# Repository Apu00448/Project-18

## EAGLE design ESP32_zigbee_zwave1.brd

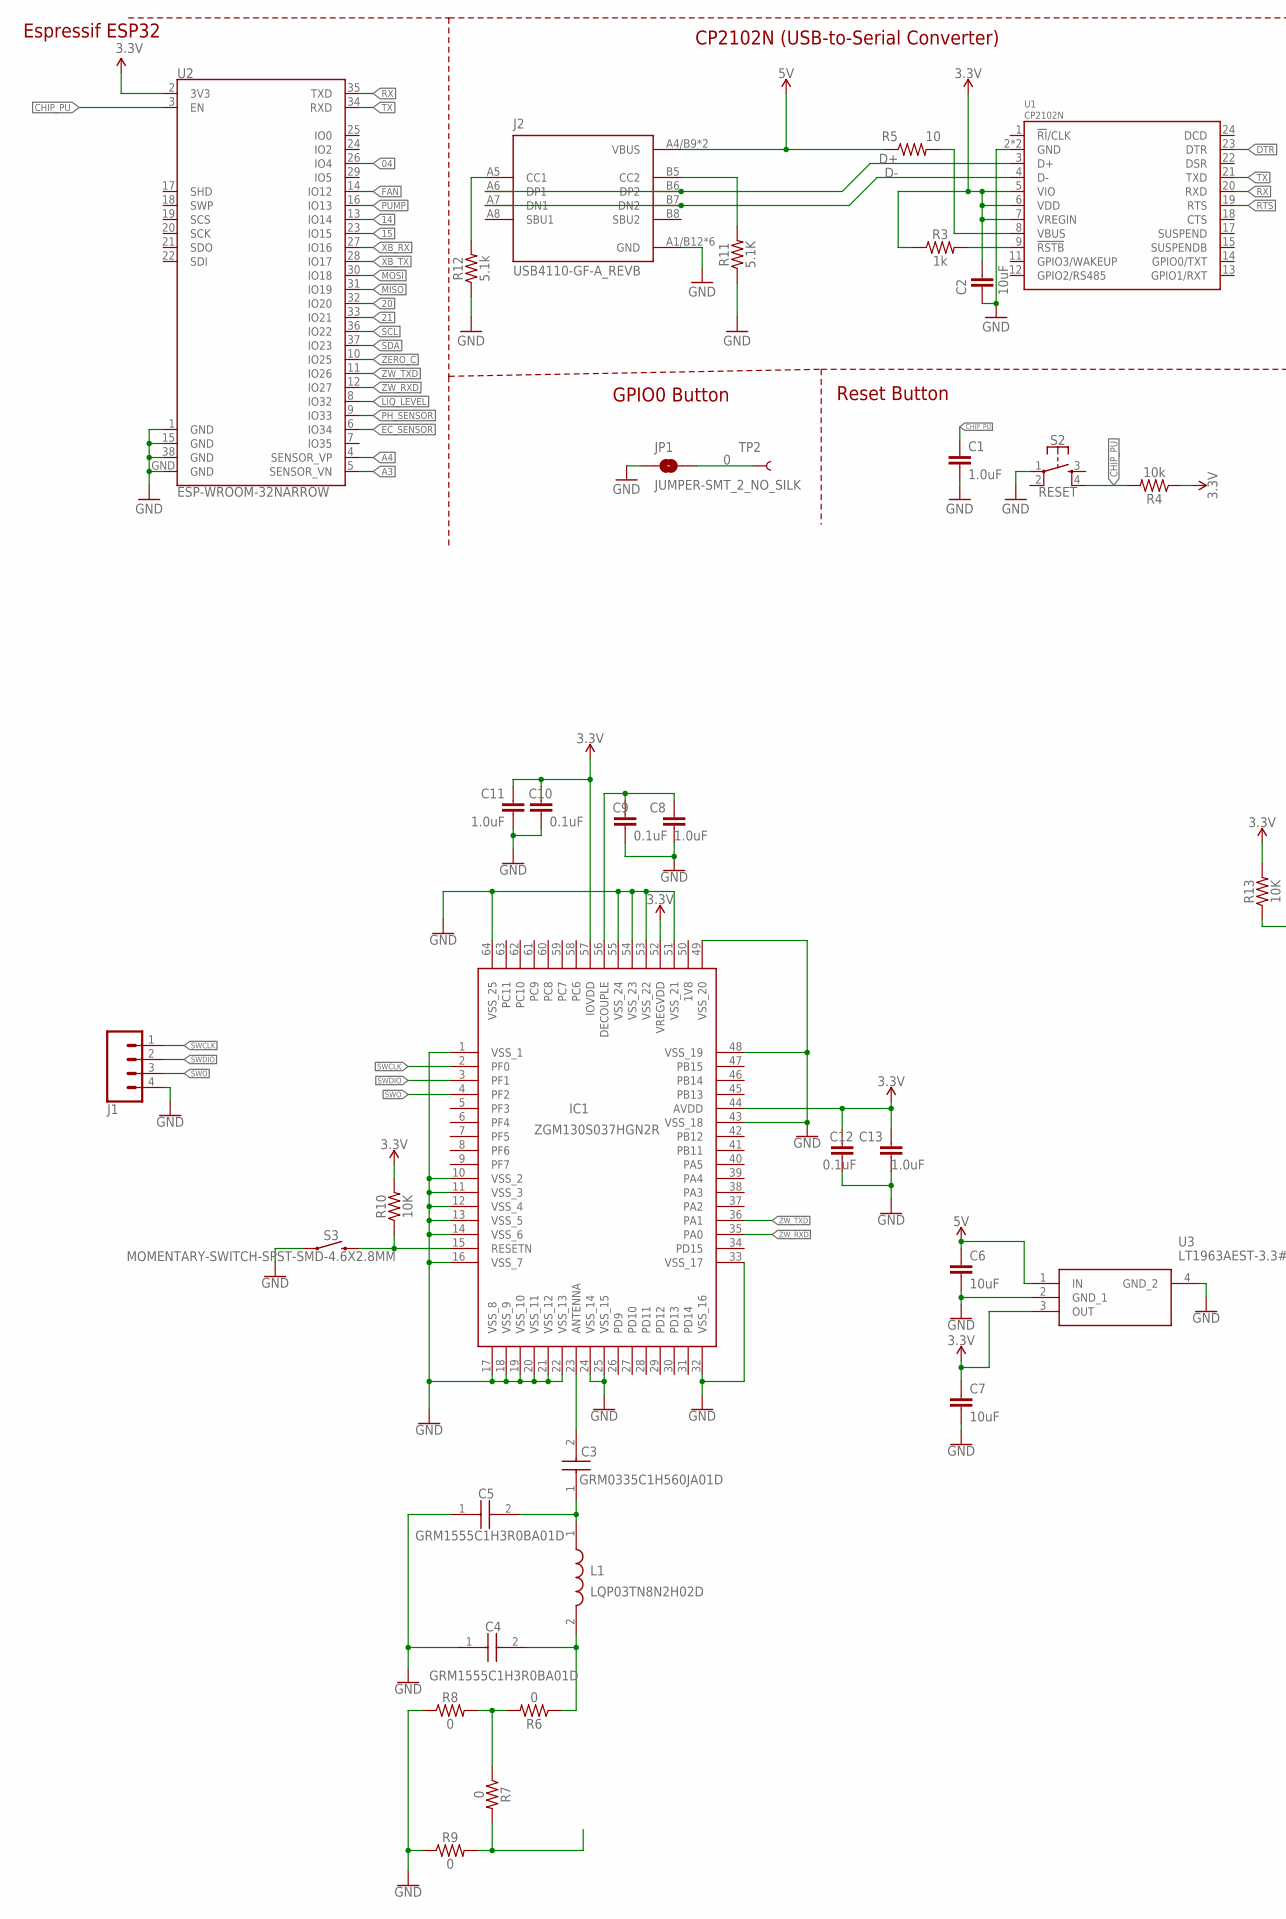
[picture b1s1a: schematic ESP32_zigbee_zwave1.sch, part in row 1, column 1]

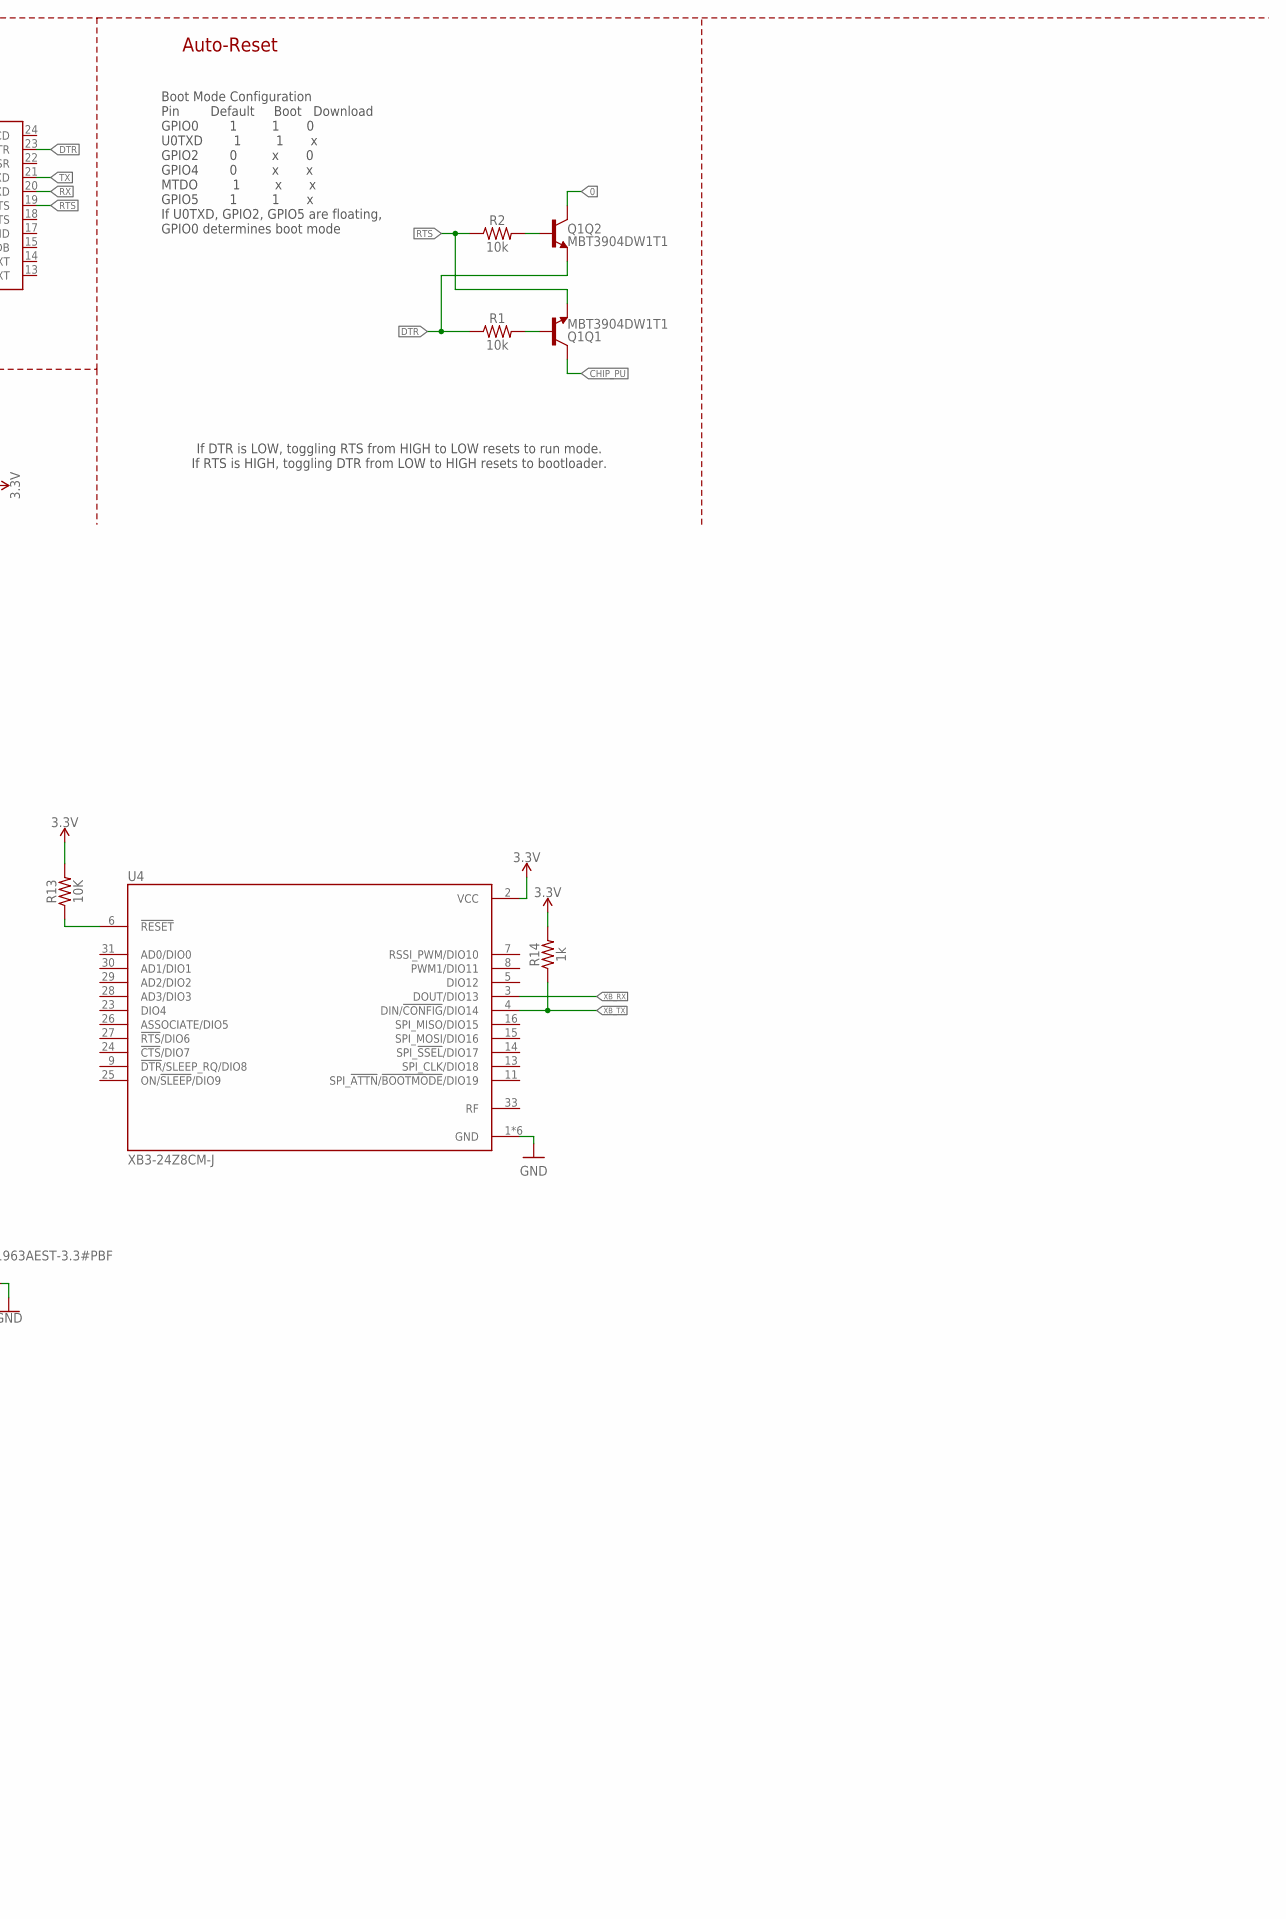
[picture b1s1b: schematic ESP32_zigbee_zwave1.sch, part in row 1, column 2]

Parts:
C1, C8, C11, C13: 1.0uF; 0402-TIGHT
C2, C6, C7: 10uF; 0402-TIGHT
C3: GRM0335C1H560JA01D; CAPC0603X33N
C4, C5: GRM1555C1H3R0BA01D; CAPC1005X55N
C9, C10, C12: 0.1uF; 0402-TIGHT
IC1: ZGM130S037HGN2R
J1: CONN_041X04_NO_SILK; 1X04_NO_SILK
J2: USB4110-GF-A_REVB; GCT_USB4110-GF-A_REVB
JP1: JUMPER-SMT_2_NO_SILK; SMT-JUMPER_2_NO_SILK
L1: LQP03TN8N2H02D; LQP03TG3N1B02D
Q1: MBT3904DW1T1; SC70-6
R1, R2, R4: 10k; 0402-TIGHT
R3, R14: 1k; 0402-TIGHT
R5: 10; 0603
R6, R7, R8, R9: 0; 0402-TIGHT
R10, R13: 10K; 0402-TIGHT
R11: 5.1K; 0402-TIGHT
R12: 5.1k; 0402-TIGHT
S2: RESET; TACTILE_SWITCH_SMD_4.6X2.8MM
S3: MOMENTARY-SWITCH-SPST-SMD-4.6X2.8MM; TACTILE_SWITCH_SMD_4.6X2.8MM
TP2: TEST-POINTTP_15TH_THRU; TP_15TH
U1: CP2102N; QFN24
U2: ESP-WROOM-32NARROW; ESP-WROOM-32-NARROW
U3: LT1963AEST-3.3#PBF; SOT230P700X180-4N
U4: XB3-24Z8CM-J; XCVR_XB3-24Z8CM-J

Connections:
0: JP1.2, Q1.6 (C), TP2.P$1
3.3V: C2.1, C7.1, C10.1, C11.2, C12.1, C13.2, IC1.44 (AVDD), IC1.52 (VREGVDD), IC1.57 (IOVDD), R3.1, R4.1, R10.2, R13.2, R14.2, U1.5 (VIO), U1.6 (VDD), U1.7 (VREGIN), U2.2 (3V3), U3.3 (OUT), U4.2 (VCC)
04: U2.26 (IO4)
5V: C6.1, J2.A4/B9 (VBUS), J2.B4/A9 (VBUS), R5.1, U3.1 (IN)
14: U2.13 (IO14)
15: U2.23 (IO15)
20: U2.32 (IO20)
21: U2.33 (IO21)
A3: U2.5 (SENSOR_VN)
A4: U2.4 (SENSOR_VP)
CHIP_PU: C1.1, Q1.3 (C), R4.2, S2.4, U2.3 (EN)
D+: J2.A6 (DP1), J2.B6 (DP2), U1.3 (D+)
D-: J2.A7 (DN1), J2.B7 (DN2), U1.4 (D-)
DTR: Q1.1 (E), R1.1, U1.23 (DTR)
EC_SENSOR: U2.6 (IO34)
FAN: U2.14 (IO12)
GND: C1.2, C2.2, C4.1, C5.1, C6.2, C7.2, C8.1, C9.2, C10.2, C11.1, C12.2, C13.1, IC1.1 (VSS_1), IC1.10 (VSS_2), IC1.11 (VSS_3), IC1.12 (VSS_4), IC1.13 (VSS_5), IC1.14 (VSS_6), IC1.16 (VSS_7), IC1.17 (VSS_8), IC1.18 (VSS_9), IC1.19 (VSS_10), IC1.20 (VSS_11), IC1.21 (VSS_12), IC1.22 (VSS_13), IC1.24 (VSS_14), IC1.25 (VSS_15), IC1.32 (VSS_16), IC1.33 (VSS_17), IC1.43 (VSS_18), IC1.48 (VSS_19), IC1.49 (VSS_20), IC1.51 (VSS_21), IC1.53 (VSS_22), IC1.54 (VSS_23), IC1.55 (VSS_24), IC1.64 (VSS_25), J1.4, J2.A1/B12 (GND), J2.B1/A12 (GND), J2.S1 (GND), J2.S2 (GND), J2.S3 (GND), J2.S4 (GND), JP1.1, R8.1, R9.1, R11.1, R12.1, S2.1, S3.1, S3.2 (1), U1.2 (GND), U1.PAD (GND), U2.1 (GND), U2.15 (GND), U2.38 (GND), U2.GND, U3.2 (GND_1), U3.4 (GND_2), U4.1 (GND), U4.10 (GND), U4.12 (GND), U4.21 (GND), U4.32 (GND), U4.34 (GND)
LIQ_LEVEL: U2.8 (IO32)
MISO: U2.31 (IO19)
MOSI: U2.30 (IO18)
unnamed: Q1.5 (B), R1.2
unnamed: Q1.2 (B), R2.2
unnamed: R3.2, U1.9 (!RSTB)
unnamed: R5.2, U1.8 (VBUS)
unnamed: C3.2, IC1.23 (ANTENNA)
unnamed: C3.1, C5.2, L1.1
unnamed: C4.2, L1.2, R6.1
unnamed: R6.2, R7.1, R8.2
unnamed: R7.2, R9.2
unnamed: IC1.15 (RESETN), R10.1, S3.3 (2), S3.4 (2)
unnamed: J2.B5 (CC2), R11.2
unnamed: J2.A5 (CC1), R12.2
unnamed: R13.1, U4.6 (!RESET)
unnamed: C8.2, C9.1, IC1.56 (DECOUPLE)
PH_SENSOR: U2.9 (IO33)
PUMP: U2.16 (IO13)
RTS: Q1.4 (E), R2.1, U1.19 (RTS)
RX: U1.20 (RXD), U2.35 (TXD)
SCL: U2.36 (IO22)
SDA: U2.37 (IO23)
SWCLK: IC1.2 (PF0), J1.1
SWDIO: IC1.3 (PF1), J1.2
SWO: IC1.4 (PF2), J1.3
TX: U1.21 (TXD), U2.34 (RXD)
XB_RX: U2.27 (IO16), U4.3 (DOUT/DIO13)
XB_TX: R14.1, U2.28 (IO17), U4.4 (DIN/!CONFIG!/DIO14)
ZERO_C: U2.10 (IO25)
ZW_RXD: IC1.35 (PA0), U2.12 (IO27)
ZW_TXD: IC1.36 (PA1), U2.11 (IO26)

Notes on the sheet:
Boot Mode Configuration Pin Default Boot Download GPIO0 1 1 0 U0TXD 1 1 x GPIO2 0 x 0 GPIO4 0 x x MTDO 1 x x GPIO5 1 1 x If U0TXD, GPIO2, GPIO5 are floating, GPIO0 determines boot mode
CP2102N (USB-to-Serial Converter)
Auto-Reset
Espressif ESP32
Reset Button
If DTR is LOW, toggling RTS from HIGH to LOW resets to run mode. If RTS is HIGH, toggling DTR from LOW to HIGH resets to bootloader.
GPIO0 Button

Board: 2 copper layers, 40 parts (0 on the bottom side), 32 nets, no tracks yet.

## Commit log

2024-01-03 ESP32_Zigbee_Zwave - Eagle

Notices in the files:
parts and their libraries:
SparkFun-Resistors: Licensing: Creative Commons ShareAlike 4.0 International - https://creativecommons.org/licenses/by-sa/4.0
